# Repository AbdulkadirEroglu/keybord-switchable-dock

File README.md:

# Dual-PC Keyboard Router & Wireless Control Pad

A custom hardware project for sharing one physical USB keyboard between two computers while adding a detachable wireless control pad for call controls, media controls, macros, status feedback, and target selection.

The design prioritizes **reliability, recoverability, wired PC connections, explicit physical control, and independent debug paths**.

## System Overview

The project consists of two custom devices:

1. **Main Dock / Keyboard Router (v2)**
   - Accepts a normal USB keyboard (USB-C).
   - Connects to both Personal and Work PCs over USB and appears as a keyboard to each.
   - Routes keyboard/HID reports to the selected target.
   - Receives the pad's events and selector state over BLE.
   - Powered by its own **USB-C PD charger** (asks for 9 V; a 30 W charger is used). It never draws power from, or back-feeds, the PCs.
   - Chips on the board, built by **JLCPCB** (machine assembly); two through-hole parts are hand-soldered.

2. **Wireless Control Pad** (to be redesigned; current plan below)
   - Detachable and battery powered.
   - 12 mechanical keys.
   - Two rotary encoders with push switches.
   - 36 addressable RGB LEDs.
   - 1.69" colour IPS display (SPI).
   - Physical `PERSONAL | OFF | WORK` metal toggle switch.
   - Li-ion 21700 battery pack, charged while docked.
   - BLE is the normal data link; the pogo UART is reserved for diagnostics/recovery.

## High-Level Architecture

```text
┌──────────── WIRELESS CONTROL PAD ────────────┐
│ Pico 2 WH (RP2350 + CYW43439)   [v1 plan]    │
│ keys, encoders, RGB, display, selector,      │
│ battery + charger                            │
└──────────┬──────────────────────┬────────────┘
           │ BLE                  │ 7-pin magnetic pogo (5 V, DET, UART)
           ▼                      ▼
┌────────────────────── MAIN DOCK (v2) ──────────────────────┐
│ ESP32-C3-MINI-1 (BLE) ── UART ──┐                          │
│                                 ▼                          │
│ keyboard ═ USB-C ═ PIO-USB ═► RP2354A A ═ USB ═► PERSONAL  │
│                                 │ UART, RUN, BOOTSEL, SWD  │
│                                 ▼                          │
│                             RP2354A B ═══ USB ═► WORK      │
│                                                            │
│ USB-C PD charger ─ CH224A (9 V) ─ TPS54331 5 V ─ 3.3 V LDO │
└────────────────────────────────────────────────────────────┘
```

## Main Hardware

### Dock (v2)

| Function | Part |
|---|---|
| Keyboard host + Personal PC endpoint | RP2354A **A** (RP2350 with 2 MB flash, QFN-60): Pico-PIO-USB host + native USB device |
| Work PC endpoint | RP2354A **B** (native USB device) |
| BLE to the pad | ESP32-C3-MINI-1-H4X module (pre-certified, PCB antenna), UART to A |
| Power input | USB-C, CH224A PD sink (9 V, I2C status to A), SMBJ15A TVS |
| 5 V | TPS54331 buck (5.16 V, 3 A), SLO0630H6R8MTT 6.8 µH, SS54 |
| 3.3 V | AMS1117-3.3 |
| Keyboard VBUS | SY6280AAC, 1.0 A, switched on only when a keyboard is detected on CC |
| Pad 5 V (pogo) | SY6280AAC, 1.45 A, switched on in hardware when the pad is docked (DET) |
| ESD | TPD4E1U06 on every USB-C port and the pogo contacts |
| Connectors | 4 × USB-C (TYPE-C-31-M-12); 7-pin JST-XH header to the pogo board in the dock lid (straight 7-pin magnetic pogo contacts) |
| Crystals | ABM8-272-T3 (Raspberry Pi's recommended part) |

Every part, its value and LCSC number: [`hardware/dock-v2/DOCK_CONNECTIONS.md`](hardware/dock-v2/DOCK_CONNECTIONS.md). Why each was chosen: `docs/dock-v2-*.md`.

### Pad (v1 plan, to be redesigned)

| Function | Selected Part / Design |
|---|---|
| Pad MCU / wireless | Raspberry Pi Pico 2 WH, socketed (on-board buck-boost 3.3 V) |
| Pad GPIO expander | TCA9555 |
| Pad charger | TP4056 (switchable ≈ 146 / 510 mA, NTC 0–45 °C, Pico-controlled enable for a 70–80 % docked window) |
| Pad power path | TPS2116 (pogo 5 V priority, battery fallback) |
| Cell protection | DW01A + FS8205A |
| Battery | 2 × Samsung SDI INR21700-50E in parallel (3.6 V, ≈ 9.8 Ah Li-ion), dual 21700 holder |
| RGB 5 V boost | TPS61023 |
| RGB logic buffer | SN74AHCT1G125 |
| RGB LEDs | 36 × SK6812MINI-E (reverse mount) |
| Keys | 12 × Razer Yellow Linear (3-pin MX) in Kailh hot-swap sockets, FR4 plate |
| Encoders | 2 × Bourns PEC11R-4220F-S0024 (24 detents, push switch) |
| Target selector | Metal SPDT ON-OFF-ON toggle |
| Display | 1.69" 240×280 IPS TFT, ST7789, SPI, PWM backlight |

## Target Selection

The physical selector is located on the **control pad**, not the dock.

```text
PERSONAL
   │
  OFF
   │
 WORK
```

The mechanical switch is the source of truth. Its state travels:

```text
Toggle → Pad → BLE → ESP32-C3 → UART → RP2354A A
```

If the pad/BLE connection is lost, the dock must eventually release all active HID states and enter `OFF`.

## Communications

- Keyboard → RP2354A A: USB host (Pico-PIO-USB)
- RP2354A A → Personal PC: USB HID (native USB)
- RP2354A A ↔ RP2354A B: 1 Mbaud+ UART; B → Work PC: USB HID
- Pad ↔ dock: BLE (ESP32-C3 central, pad peripheral), ESP32-C3 ↔ A: UART
- Pogo UART (A's PIO UART): debug/recovery only

The internal UART protocol uses framed binary packets:

```text
SOF | TYPE | SEQ | LEN | PAYLOAD | CRC
```

Normal HID reports may be fire-and-forget. Critical control operations can require acknowledgement.

## Fail-Safe Philosophy

The design should fail toward **released keys and no routing**, not toward a stuck input.

- Target change → release the previous endpoint before changing the route.
- `OFF` → release both endpoints.
- BLE/pad timeout → release all and route OFF.
- A ↔ B link timeout → B sends a released state and idles; A can reset B.
- Keyboard faults → A power-cycles the keyboard's VBUS.
- Every MCU has a physical recovery path, and A can reflash B (SWD) and the ESP32-C3 (UART) from the Personal PC.

## Mechanical Baseline

- **Dock:** PCB 100 × 100 mm, 2 layers. PC cables leave at the back, the keyboard at the left, the charger at the right. **The pad sits on top of the dock:** the pogo contacts are on a small board in the dock lid, cabled to the dock board.
- **Pad (v1 plan):** wedge enclosure ≈ 160 × 110–120 mm, front ≈ 25 mm, back ≈ 44 mm, battery at the back under the display/encoder row.

Docking contacts (dock side), magnets on both sides:

```text
GND | +5V | DET | RX | TX | +5V | GND
```

## Repository Layout

```text
dock-pad/
├── hardware/
│   ├── dock-v2/        v2 dock: KiCad project, DOCK_CONNECTIONS.md, PCB_PLACEMENT.md
│   ├── dock/           v1 dock (Pico modules), reference
│   ├── pad/            pad (v1 plan)
│   ├── pogo/           pad pogo board
│   ├── libraries/      shared symbols/footprints/3D models (THIRD_PARTY.md)
│   ├── reference/      Raspberry Pi RP2350A Minimal design (MIT)
│   └── tools/          RPi core-layout copy script, dock v2 connection model and wiring checker
├── mechanical/
├── firmware/
├── datasheets/
├── docs/               dock v2 design decisions (dock-v2-*.md), pad drawings
├── README.md
└── DESIGN.md
```

## Current Project State

- **Dock v2 (branch `dock-v2`):** every part decided and placed on the six schematic sheets (154 parts, values, footprints, LCSC numbers). Next: wiring the schematic by hand from [DOCK_WIRING.md](hardware/dock-v2/DOCK_WIRING.md) (component by component; the circuit is explained in DOCK_CONNECTIONS.md) (checked with `hardware/tools/dock_v2_connections/check_wiring.py`), then placement and routing on a 4-layer board. The order cost will be calculated when the PCB is ready.
- **Pad:** being redesigned. Decided so far: **ESP32-S3-MINI-1-N8** (MCU + BLE, JLC assembly), the pad **sits on top of the dock** with its pogo board in the floor, **1 × 21700-50E** with an **ETA6003** switching charger (power path), charged only on the dock, TLV75733P 3.3 V LDO, direct-GPIO keys/encoders, SK6812MINI-E + XL-2020 LEDs on a TPS61023 5 V boost, Meon 1.69" ST7789 module. Decisions: `docs/pad-v2-*.md`. The rest of `hardware/pad/` is still the v1 plan.
- **v1 dock:** complete (routed, DRC clean) on `master`; superseded by v2.

See [DESIGN.md](DESIGN.md) for the engineering baseline.

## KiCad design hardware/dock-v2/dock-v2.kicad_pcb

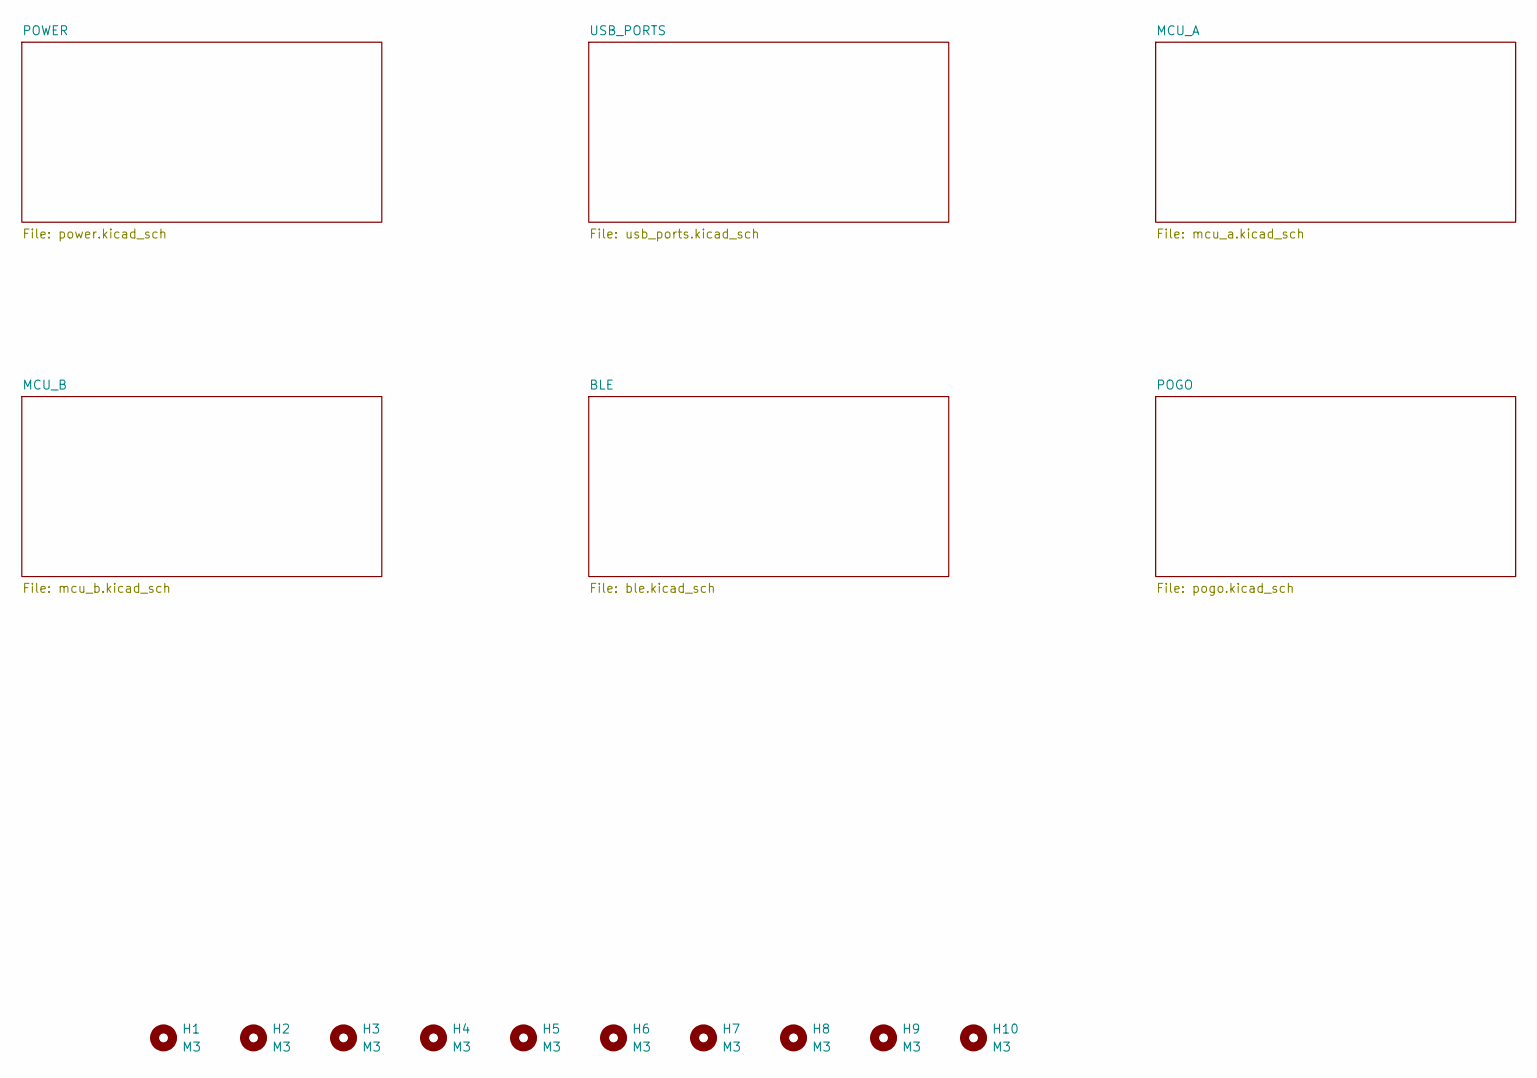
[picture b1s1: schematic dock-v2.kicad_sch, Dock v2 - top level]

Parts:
H1, H2, H3, H4, H5, H6, H7, H8, H9, H10: M3; MountingHole_3.2mm_M3

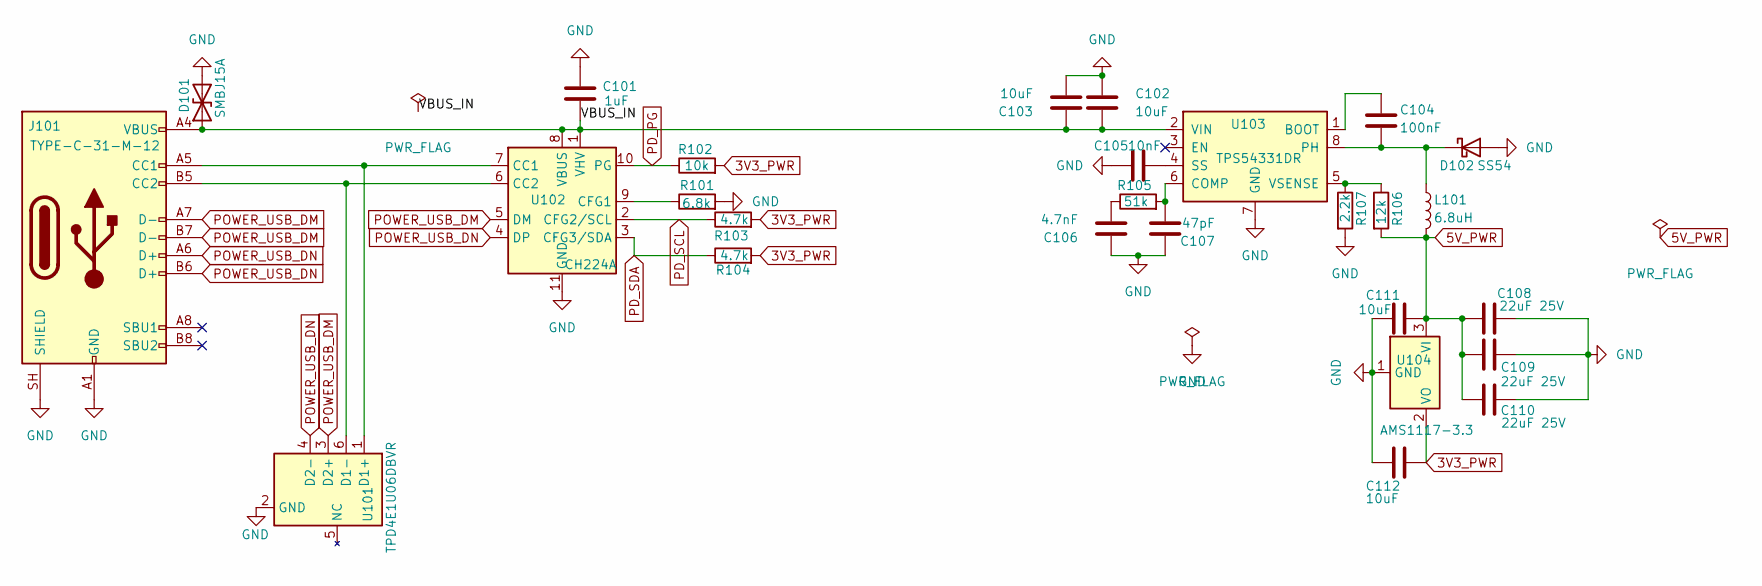
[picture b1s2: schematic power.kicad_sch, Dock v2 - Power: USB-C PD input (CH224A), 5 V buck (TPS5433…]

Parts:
C101: 1uF; C_0603_1608Metric; LCSC C15849
C102, C103, C111, C112: 10uF; C_0805_2012Metric; LCSC C15850
C104: 100nF; C_0402_1005Metric; LCSC C1525
C105: 10nF; C_0402_1005Metric; LCSC C15195
C106: 4.7nF; C_0402_1005Metric; LCSC C1538
C107: 47pF; C_0402_1005Metric; LCSC C1567
C108, C109, C110: 22uF 25V; C_1206_3216Metric; LCSC C12891
D101: SMBJ15A; D_SMB; LCSC C113988
D102: SS54; D_SMC; LCSC C22452
J101: TYPE-C-31-M-12; USB_C_Receptacle_HRO_TYPE-C-31-M-12; LCSC C165948
L101: 6.8uH; L_TechFuse_SL0630; LCSC C207841
R101: 6.8k; R_0402_1005Metric; LCSC C25917
R102: 10k; R_0402_1005Metric; LCSC C25744
R103, R104: 4.7k; R_0402_1005Metric; LCSC C25900
R105: 51k; R_0402_1005Metric; LCSC C25794
R106: 12k; R_0402_1005Metric; LCSC C25752
R107: 2.2k; R_0402_1005Metric; LCSC C25879
U101: TPD4E1U06DBVR; SOT-23-6; LCSC C124691
U102: CH224A; SSOP-10-1EP_3.9x4.9mm_P1mm_EP2.1x3.3mm; LCSC C42459160
U103: TPS54331DR; SOIC-8_3.9x4.9mm_P1.27mm; LCSC C9865
U104: AMS1117-3.3; SOT-223-3_TabPin2; LCSC C6186

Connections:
3V3_PWR: C112.1, R102.2, R103.2, R104.2, U104.2 (VO); also elsewhere on the board
5V_PWR: C108.1, C109.2, C110.1, C111.1, L101.2, R106.2, U104.3 (VI); also elsewhere on the board
/POWER/VBUS_IN: C101.2, C102.2, C103.1, D101.1 (A1), J101.A4 (VBUS), J101.A9 (VBUS), J101.B4 (VBUS), J101.B9 (VBUS), U102.1 (VHV), U102.8 (VBUS), U103.2 (VIN)
GND: C101.1, C102.1, C103.2, C105.1, C106.1, C107.1, C108.2, C109.1, C110.2, C111.2, C112.2, D101.2 (A2), D102.2 (A), J101.A1 (GND), J101.A12 (GND), J101.B1 (GND), J101.B12 (GND), J101.SH (SHIELD), R101.2, R107.2, U101.2 (GND), U102.11 (GND), U103.7 (GND), U104.1 (GND); also elsewhere on the board
unnamed: C106.2, R105.1
unnamed: C104.2, D102.1 (K), L101.1, U103.8 (PH)
unnamed: J101.A5 (CC1), U101.1 (D1+), U102.7 (CC1)
unnamed: J101.B5 (CC2), U101.6 (D1-), U102.6 (CC2)
unnamed: R101.1, U102.9 (CFG1)
unnamed: C104.1, U103.1 (BOOT)
unnamed: C107.2, R105.2, U103.6 (COMP)
unnamed: C105.2, U103.4 (SS)
unnamed: R106.1, R107.1, U103.5 (VSENSE)
PD_PG: R102.1, U102.10 (PG); also elsewhere on the board
PD_SCL: R103.1, U102.2 (CFG2/SCL); also elsewhere on the board
PD_SDA: R104.1, U102.3 (CFG3/SDA); also elsewhere on the board
POWER_USB_DM: J101.A7 (D-), J101.B7 (D-), U101.3 (D2+), U102.5 (DM)
POWER_USB_DN: J101.A6 (D+), J101.B6 (D+), U101.4 (D2-), U102.4 (DP)

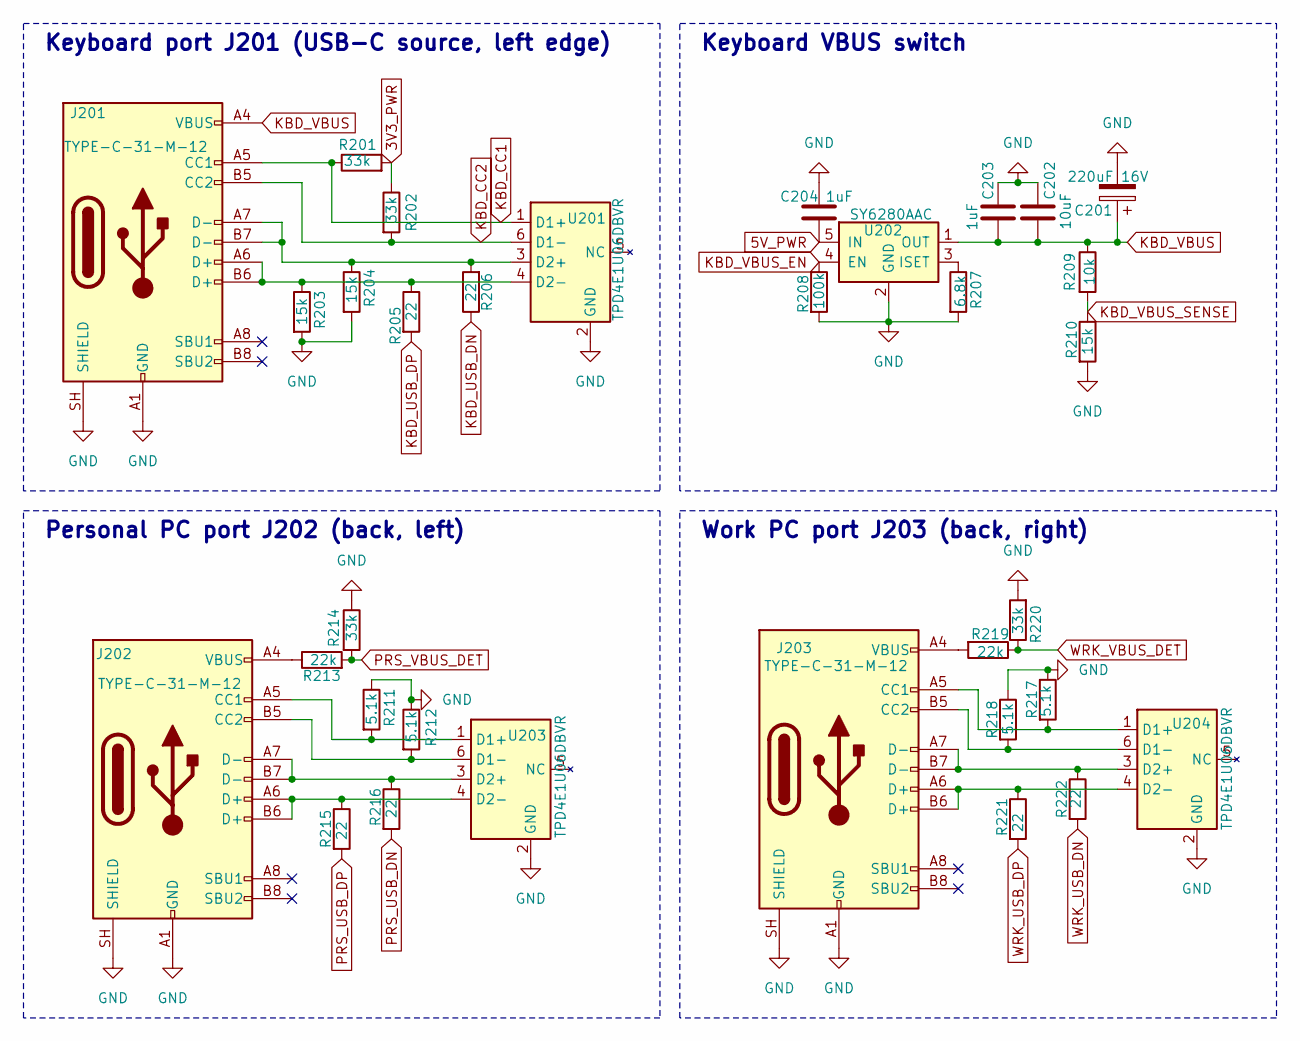
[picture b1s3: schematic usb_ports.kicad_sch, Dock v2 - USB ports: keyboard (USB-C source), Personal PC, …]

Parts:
C201: 220uF 16V; CP_Radial_D6.3mm_P5.00mm
C202: 10uF; C_0805_2012Metric; LCSC C15850
C203, C204: 1uF; C_0402_1005Metric; LCSC C52923
J201, J202, J203: TYPE-C-31-M-12; USB_C_Receptacle_HRO_TYPE-C-31-M-12; LCSC C165948
R201, R202, R214, R220: 33k; R_0402_1005Metric; LCSC C25779
R203, R204, R210: 15k; R_0402_1005Metric; LCSC C25756
R205, R206, R215, R216, R221, R222: 22; R_0402_1005Metric; LCSC C25092
R207: 6.8k; R_0402_1005Metric; LCSC C25917
R208: 100k; R_0402_1005Metric; LCSC C25741
R209: 10k; R_0402_1005Metric; LCSC C25744
R211, R212, R217, R218: 5.1k; R_0402_1005Metric; LCSC C25905
R213, R219: 22k; R_0402_1005Metric; LCSC C25768
U201, U203, U204: TPD4E1U06DBVR; SOT-23-6; LCSC C124691
U202: SY6280AAC; SOT-23-5; LCSC C55136

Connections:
3V3_PWR: R201.2, R202.1; also elsewhere on the board
5V_PWR: C204.2, U202.5 (IN); also elsewhere on the board
GND: C201.2, C202.1, C203.2, C204.1, J201.A1 (GND), J201.A12 (GND), J201.B1 (GND), J201.B12 (GND), J201.SH (SHIELD), J202.A1 (GND), J202.A12 (GND), J202.B1 (GND), J202.B12 (GND), J202.SH (SHIELD), J203.A1 (GND), J203.A12 (GND), J203.B1 (GND), J203.B12 (GND), J203.SH (SHIELD), R203.2, R204.2, R207.2, R208.2, R210.2, R211.1, R212.1, R214.1, R217.1, R218.1, R220.2, U201.2 (GND), U202.2 (GND), U203.2 (GND), U204.2 (GND); also elsewhere on the board
KBD_CC1: J201.A5 (CC1), R201.1, U201.1 (D1+); also elsewhere on the board
KBD_CC2: J201.B5 (CC2), R202.2, U201.6 (D1-); also elsewhere on the board
KBD_USB_DN: R206.1; also elsewhere on the board
KBD_USB_DP: R205.2; also elsewhere on the board
KBD_VBUS: C201.1, C202.2, C203.1, J201.A4 (VBUS), J201.A9 (VBUS), J201.B4 (VBUS), J201.B9 (VBUS), R209.1, U202.1 (OUT)
KBD_VBUS_EN: R208.1, U202.4 (EN); also elsewhere on the board
KBD_VBUS_SENSE: R209.2, R210.1; also elsewhere on the board
unnamed: J202.A5 (CC1), R211.2, U203.1 (D1+)
unnamed: J202.B5 (CC2), R212.2, U203.6 (D1-)
unnamed: J202.A4 (VBUS), J202.A9 (VBUS), J202.B4 (VBUS), J202.B9 (VBUS), R213.1
unnamed: J203.A5 (CC1), R217.2, U204.1 (D1+)
unnamed: J203.B5 (CC2), R218.2, U204.6 (D1-)
unnamed: J203.A4 (VBUS), J203.A9 (VBUS), J203.B4 (VBUS), J203.B9 (VBUS), R219.2
unnamed: J201.A7 (D-), J201.B7 (D-), R204.1, R206.2, U201.3 (D2+)
unnamed: J201.A6 (D+), J201.B6 (D+), R203.1, R205.1, U201.4 (D2-)
unnamed: R207.1, U202.3 (ISET)
unnamed: J202.A7 (D-), J202.B7 (D-), R216.1, U203.3 (D2+)
unnamed: J202.A6 (D+), J202.B6 (D+), R215.1, U203.4 (D2-)
unnamed: J203.A7 (D-), J203.B7 (D-), R222.1, U204.3 (D2+)
unnamed: J203.A6 (D+), J203.B6 (D+), R221.1, U204.4 (D2-)
PRS_USB_DN: R216.2; also elsewhere on the board
PRS_USB_DP: R215.2; also elsewhere on the board
PRS_VBUS_DET: R213.2, R214.2; also elsewhere on the board
WRK_USB_DN: R222.2; also elsewhere on the board
WRK_USB_DP: R221.2; also elsewhere on the board
WRK_VBUS_DET: R219.1, R220.1; also elsewhere on the board

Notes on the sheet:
Keyboard VBUS switch
Keyboard port J201 (USB-C source, left edge)
Personal PC port J202 (back, left)
Work PC port J203 (back, right)

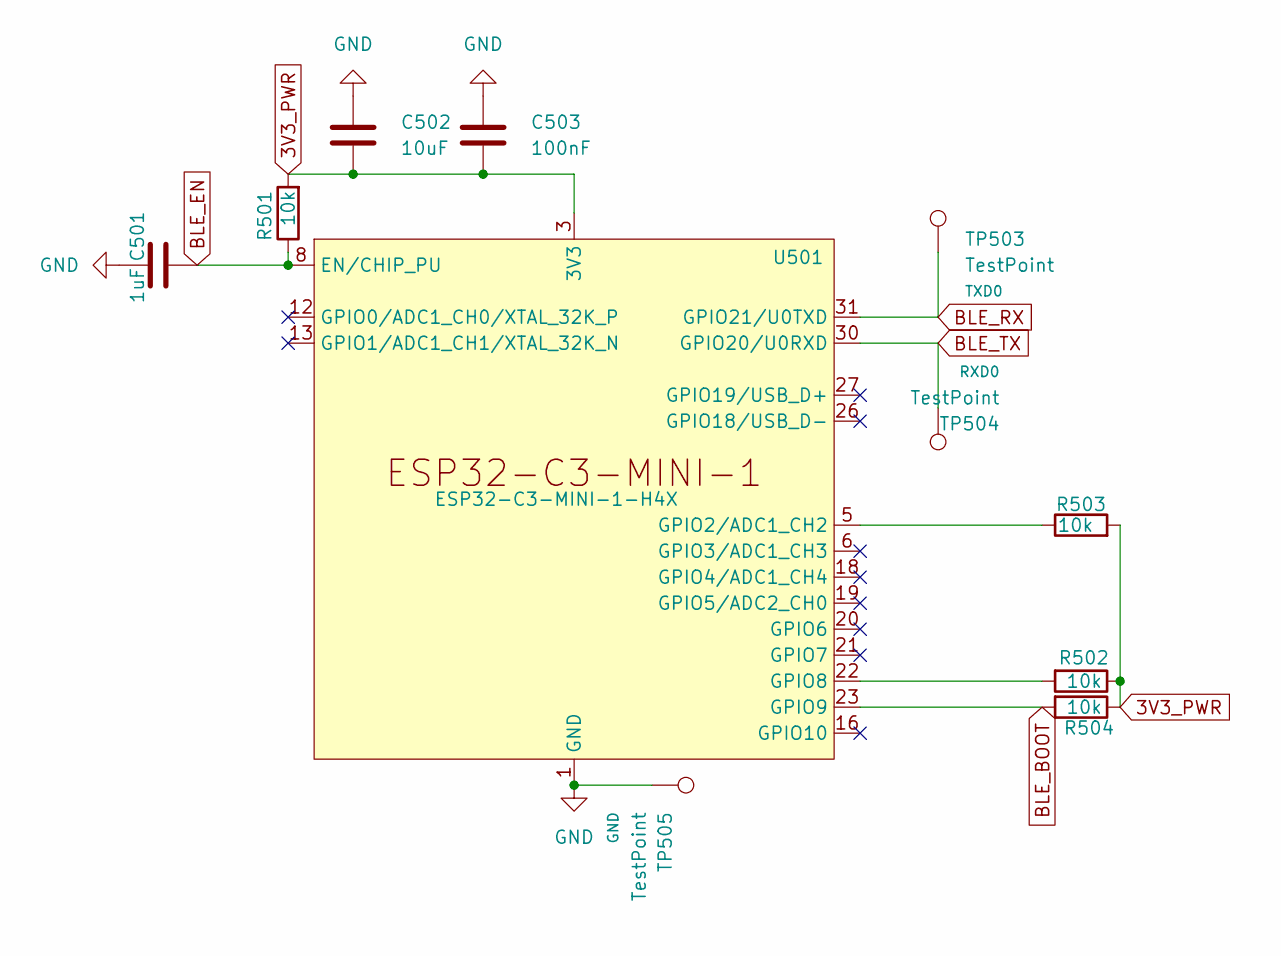
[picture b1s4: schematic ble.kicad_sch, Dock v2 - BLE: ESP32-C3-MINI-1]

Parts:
C501: 1uF; C_0402_1005Metric; LCSC C52923
C502: 10uF; C_0805_2012Metric; LCSC C15850
C503: 100nF; C_0402_1005Metric; LCSC C1525
R501, R502, R503, R504: 10k; R_0402_1005Metric; LCSC C25744
TP503, TP504, TP505: TestPoint; TestPoint_Pad_D1.0mm
U501: ESP32-C3-MINI-1-H4X; ESP32-C3-MINI-1; LCSC C41349510

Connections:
3V3_PWR: C502.2, C503.2, R501.2, R502.1, R503.2, R504.1, U501.3 (3V3); also elsewhere on the board
BLE_BOOT: R504.2, U501.23 (GPIO9); also elsewhere on the board
BLE_EN: C501.2, R501.1, U501.8 (EN/CHIP_PU); also elsewhere on the board
BLE_RX: TP503.1 (1_1), U501.31 (GPIO21/U0TXD); also elsewhere on the board
BLE_TX: TP504.1 (1_1), U501.30 (GPIO20/U0RXD); also elsewhere on the board
GND: C501.1, C502.1, C503.1, TP505.1 (1_1), U501.1 (GND), U501.2 (GND), U501.11 (GND), U501.14 (GND), U501.36 (GND), U501.37 (GND), U501.38 (GND), U501.39 (GND), U501.40 (GND), U501.41 (GND), U501.42 (GND), U501.43 (GND), U501.44 (GND), U501.45 (GND), U501.46 (GND), U501.47 (GND), U501.48 (GND), U501.49 (GND), U501.50 (GND), U501.51 (GND), U501.52 (GND), U501.53 (GND); also elsewhere on the board
unnamed: R503.1, U501.5 (GPIO2/ADC1_CH2)
unnamed: R502.2, U501.22 (GPIO8)

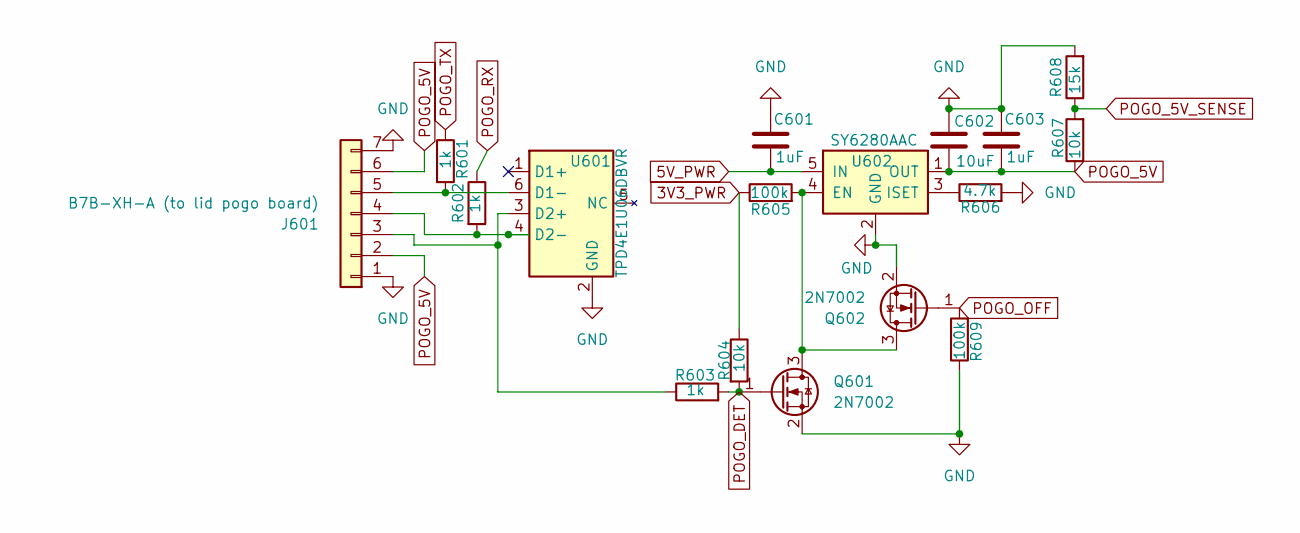
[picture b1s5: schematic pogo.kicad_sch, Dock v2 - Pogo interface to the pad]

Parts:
C601, C603: 1uF; C_0402_1005Metric; LCSC C52923
C602: 10uF; C_0805_2012Metric; LCSC C15850
J601: B7B-XH-A (to lid pogo board); JST_XH_B7B-XH-A_1x07_P2.50mm_Vertical_EdgeTrim; LCSC C144398
Q601, Q602: 2N7002; SOT-23; LCSC C8545
R601, R602, R603: 1k; R_0402_1005Metric; LCSC C11702
R604, R607: 10k; R_0402_1005Metric; LCSC C25744
R605, R609: 100k; R_0402_1005Metric; LCSC C25741
R606: 4.7k; R_0402_1005Metric; LCSC C25900
R608: 15k; R_0402_1005Metric; LCSC C25756
U601: TPD4E1U06DBVR; SOT-23-6; LCSC C124691
U602: SY6280AAC; SOT-23-5; LCSC C55136

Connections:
3V3_PWR: R604.1, R605.1; also elsewhere on the board
5V_PWR: C601.2, U602.5 (IN); also elsewhere on the board
GND: C601.1, C602.1, C603.1, J601.1, J601.7, Q601.2 (S), Q602.2 (S), R606.2, R608.2, R609.1, U601.2 (GND), U602.2 (GND); also elsewhere on the board
unnamed: J601.3, R603.1, U601.3 (D2+)
unnamed: J601.4, R602.2, U601.4 (D2-)
unnamed: J601.5, R601.2, U601.6 (D1-)
unnamed: Q601.3 (D), Q602.3 (D), R605.2, U602.4 (EN)
unnamed: R606.1, U602.3 (ISET)
POGO_5V: C602.2, C603.2, J601.2, J601.6, R607.1, U602.1 (OUT)
POGO_5V_SENSE: R607.2, R608.1; also elsewhere on the board
POGO_DET: Q601.1 (G), R603.2, R604.2; also elsewhere on the board
POGO_OFF: Q602.1 (G), R609.2; also elsewhere on the board
POGO_RX: R602.1; also elsewhere on the board
POGO_TX: R601.1; also elsewhere on the board

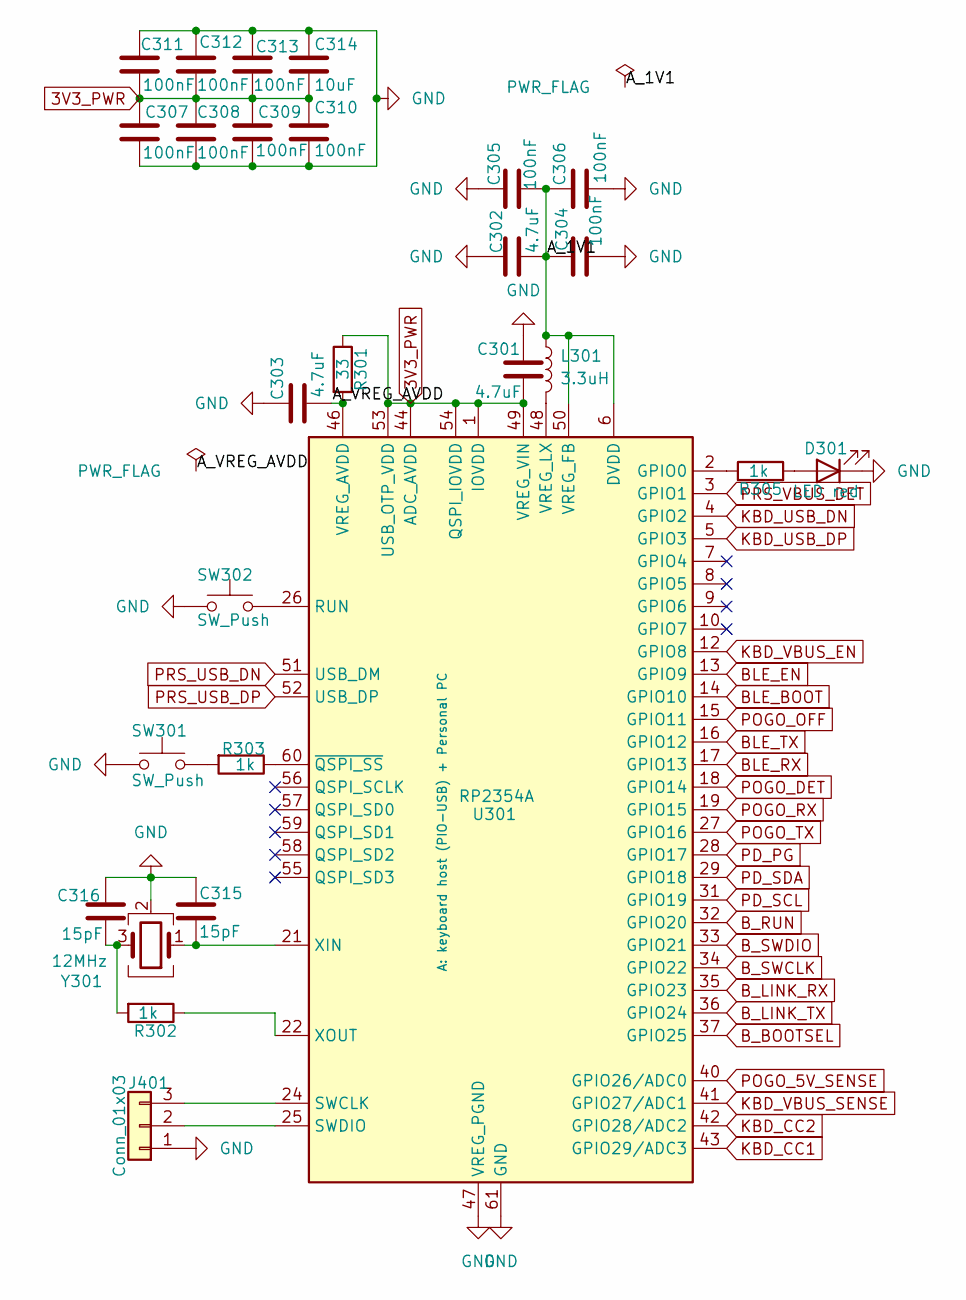
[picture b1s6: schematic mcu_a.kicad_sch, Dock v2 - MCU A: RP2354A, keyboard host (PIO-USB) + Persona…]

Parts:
C301, C302: 4.7uF; C_0402_RPi_Wide; LCSC C23733
C303: 4.7uF; C_0402_1005Metric; LCSC C23733
C304, C305, C306, C307, C308, C309, C310, C311, C312, C313: 100nF; C_0402_1005Metric; LCSC C1525
C314: 10uF; C_0805_2012Metric; LCSC C15850
C315, C316: 15pF; C_0402_1005Metric; LCSC C1548
D301: LED red; LED_0603_1608Metric; LCSC C2286
J401: Conn_01x03; PinHeader_1x03_P2.54mm_Vertical
L301: 3.3uH; L_Abracon_AOTA-B201610S3R3_0806; LCSC C42411119
R301: 33; R_0402_1005Metric; LCSC C25105
R302, R303, R305: 1k; R_0402_1005Metric; LCSC C11702
SW301, SW302: SW_Push; SW_Push_1P1T_XKB_TS-1187A; LCSC C318884
U301: RP2354A; RP2350A_QFN-60_RPi_Vias; LCSC C41378174
Y301: 12MHz; Crystal_SMD_3225-4Pin_3.2x2.5mm; LCSC C20625731

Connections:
3V3_PWR: C301.2, C307.1, C308.1, C309.1, C310.1, C311.2, C312.2, C313.2, C314.2, R301.1, U301.1 (IOVDD), U301.11 (IOVDD), U301.20 (IOVDD), U301.30 (IOVDD), U301.38 (IOVDD), U301.44 (ADC_AVDD), U301.45 (IOVDD), U301.49 (VREG_VIN), U301.53 (USB_OTP_VDD), U301.54 (QSPI_IOVDD); also elsewhere on the board
/MCU_A/A_1V1: C302.2, C304.1, C305.2, C306.1, L301.1, U301.6 (DVDD), U301.23 (DVDD), U301.39 (DVDD), U301.50 (VREG_FB)
/MCU_A/A_VREG_AVDD: C303.2, R301.2, U301.46 (VREG_AVDD)
BLE_BOOT: U301.14 (GPIO10); also elsewhere on the board
BLE_EN: U301.13 (GPIO9); also elsewhere on the board
BLE_RX: U301.17 (GPIO13); also elsewhere on the board
BLE_TX: U301.16 (GPIO12); also elsewhere on the board
B_BOOTSEL: U301.37 (GPIO25); also elsewhere on the board
B_LINK_RX: U301.35 (GPIO23); also elsewhere on the board
B_LINK_TX: U301.36 (GPIO24); also elsewhere on the board
B_RUN: U301.32 (GPIO20); also elsewhere on the board
B_SWCLK: U301.34 (GPIO22); also elsewhere on the board
B_SWDIO: U301.33 (GPIO21); also elsewhere on the board
GND: C301.1, C302.1, C303.1, C304.2, C305.1, C306.2, C307.2, C308.2, C309.2, C310.2, C311.1, C312.1, C313.1, C314.1, C315.1, C316.1, D301.1 (K), J401.1, SW301.1, SW302.1, U301.47 (VREG_PGND), U301.61 (GND), Y301.2 (G), Y301.4 (G); also elsewhere on the board
KBD_CC1: U301.43 (GPIO29/ADC3); also elsewhere on the board
KBD_CC2: U301.42 (GPIO28/ADC2); also elsewhere on the board
KBD_USB_DN: U301.4 (GPIO2); also elsewhere on the board
KBD_USB_DP: U301.5 (GPIO3); also elsewhere on the board
KBD_VBUS_EN: U301.12 (GPIO8); also elsewhere on the board
KBD_VBUS_SENSE: U301.41 (GPIO27/ADC1); also elsewhere on the board
unnamed: C316.2, R302.2, Y301.3
unnamed: D301.2 (A), R305.2
unnamed: J401.2, U301.25 (SWDIO)
unnamed: J401.3, U301.24 (SWCLK)
unnamed: R303.2, SW301.2
unnamed: R305.1, U301.2 (GPIO0)
unnamed: SW302.2, U301.26 (RUN)
unnamed: L301.2, U301.48 (VREG_LX)
unnamed: C315.2, U301.21 (XIN), Y301.1
unnamed: R302.1, U301.22 (XOUT)
unnamed: R303.1, U301.60 (~QSPI_SS)
PD_PG: U301.28 (GPIO17); also elsewhere on the board
PD_SCL: U301.31 (GPIO19); also elsewhere on the board
PD_SDA: U301.29 (GPIO18); also elsewhere on the board
POGO_5V_SENSE: U301.40 (GPIO26/ADC0); also elsewhere on the board
POGO_DET: U301.18 (GPIO14); also elsewhere on the board
POGO_OFF: U301.15 (GPIO11); also elsewhere on the board
POGO_RX: U301.19 (GPIO15); also elsewhere on the board
POGO_TX: U301.27 (GPIO16); also elsewhere on the board
PRS_USB_DN: U301.51 (USB_DM); also elsewhere on the board
PRS_USB_DP: U301.52 (USB_DP); also elsewhere on the board
PRS_VBUS_DET: U301.3 (GPIO1); also elsewhere on the board

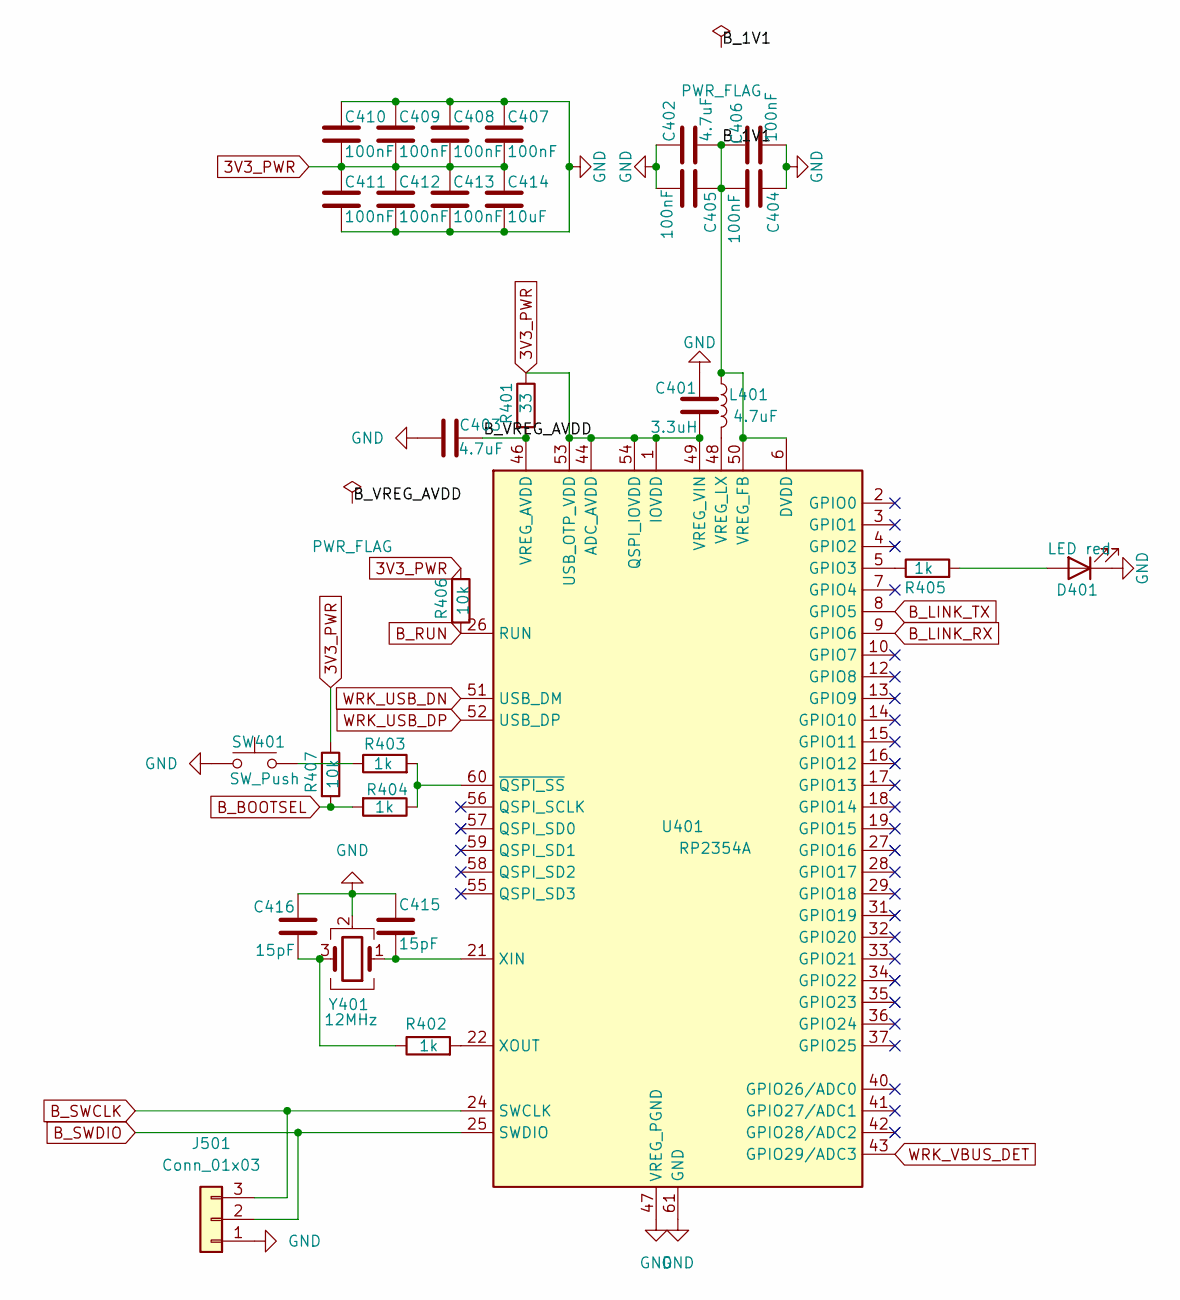
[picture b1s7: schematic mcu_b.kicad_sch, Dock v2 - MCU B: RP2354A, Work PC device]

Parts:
C401, C402: 4.7uF; C_0402_RPi_Wide; LCSC C23733
C403: 4.7uF; C_0402_1005Metric; LCSC C23733
C404, C405, C406, C407, C408, C409, C410, C411, C412, C413: 100nF; C_0402_1005Metric; LCSC C1525
C414: 10uF; C_0805_2012Metric; LCSC C15850
C415, C416: 15pF; C_0402_1005Metric; LCSC C1548
D401: LED red; LED_0603_1608Metric; LCSC C2286
J501: Conn_01x03; PinHeader_1x03_P2.54mm_Vertical
L401: 3.3uH; L_Abracon_AOTA-B201610S3R3_0806; LCSC C42411119
R401: 33; R_0402_1005Metric; LCSC C25105
R402, R403, R404, R405: 1k; R_0402_1005Metric; LCSC C11702
R406, R407: 10k; R_0402_1005Metric; LCSC C25744
SW401: SW_Push; SW_Push_1P1T_XKB_TS-1187A; LCSC C318884
U401: RP2354A; RP2350A_QFN-60_RPi_Vias; LCSC C41378174
Y401: 12MHz; Crystal_SMD_3225-4Pin_3.2x2.5mm; LCSC C20625731

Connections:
3V3_PWR: C401.2, C407.2, C408.2, C409.2, C410.2, C411.1, C412.1, C413.1, C414.1, R401.1, R406.1, R407.1, U401.1 (IOVDD), U401.11 (IOVDD), U401.20 (IOVDD), U401.30 (IOVDD), U401.38 (IOVDD), U401.44 (ADC_AVDD), U401.45 (IOVDD), U401.49 (VREG_VIN), U401.53 (USB_OTP_VDD), U401.54 (QSPI_IOVDD); also elsewhere on the board
/MCU_B/B_1V1: C402.2, C404.2, C405.1, C406.1, L401.1, U401.6 (DVDD), U401.23 (DVDD), U401.39 (DVDD), U401.50 (VREG_FB)
/MCU_B/B_VREG_AVDD: C403.2, R401.2, U401.46 (VREG_AVDD)
B_BOOTSEL: R404.2, R407.2; also elsewhere on the board
B_LINK_RX: U401.9 (GPIO6); also elsewhere on the board
B_LINK_TX: U401.8 (GPIO5); also elsewhere on the board
B_RUN: R406.2, U401.26 (RUN); also elsewhere on the board
B_SWCLK: J501.3, U401.24 (SWCLK); also elsewhere on the board
B_SWDIO: J501.2, U401.25 (SWDIO); also elsewhere on the board
GND: C401.1, C402.1, C403.1, C404.1, C405.2, C406.2, C407.1, C408.1, C409.1, C410.1, C411.2, C412.2, C413.2, C414.2, C415.1, C416.2, D401.1 (K), J501.1, SW401.1, U401.47 (VREG_PGND), U401.61 (GND), Y401.2 (G), Y401.4 (G); also elsewhere on the board
unnamed: C416.1, R402.1, Y401.3
unnamed: D401.2 (A), R405.2
unnamed: R403.1, SW401.2
unnamed: R405.1, U401.5 (GPIO3)
unnamed: L401.2, U401.48 (VREG_LX)
unnamed: C415.2, U401.21 (XIN), Y401.1
unnamed: R402.2, U401.22 (XOUT)
unnamed: R403.2, R404.1, U401.60 (~QSPI_SS)
WRK_USB_DN: U401.51 (USB_DM); also elsewhere on the board
WRK_USB_DP: U401.52 (USB_DP); also elsewhere on the board
WRK_VBUS_DET: U401.43 (GPIO29/ADC3); also elsewhere on the board

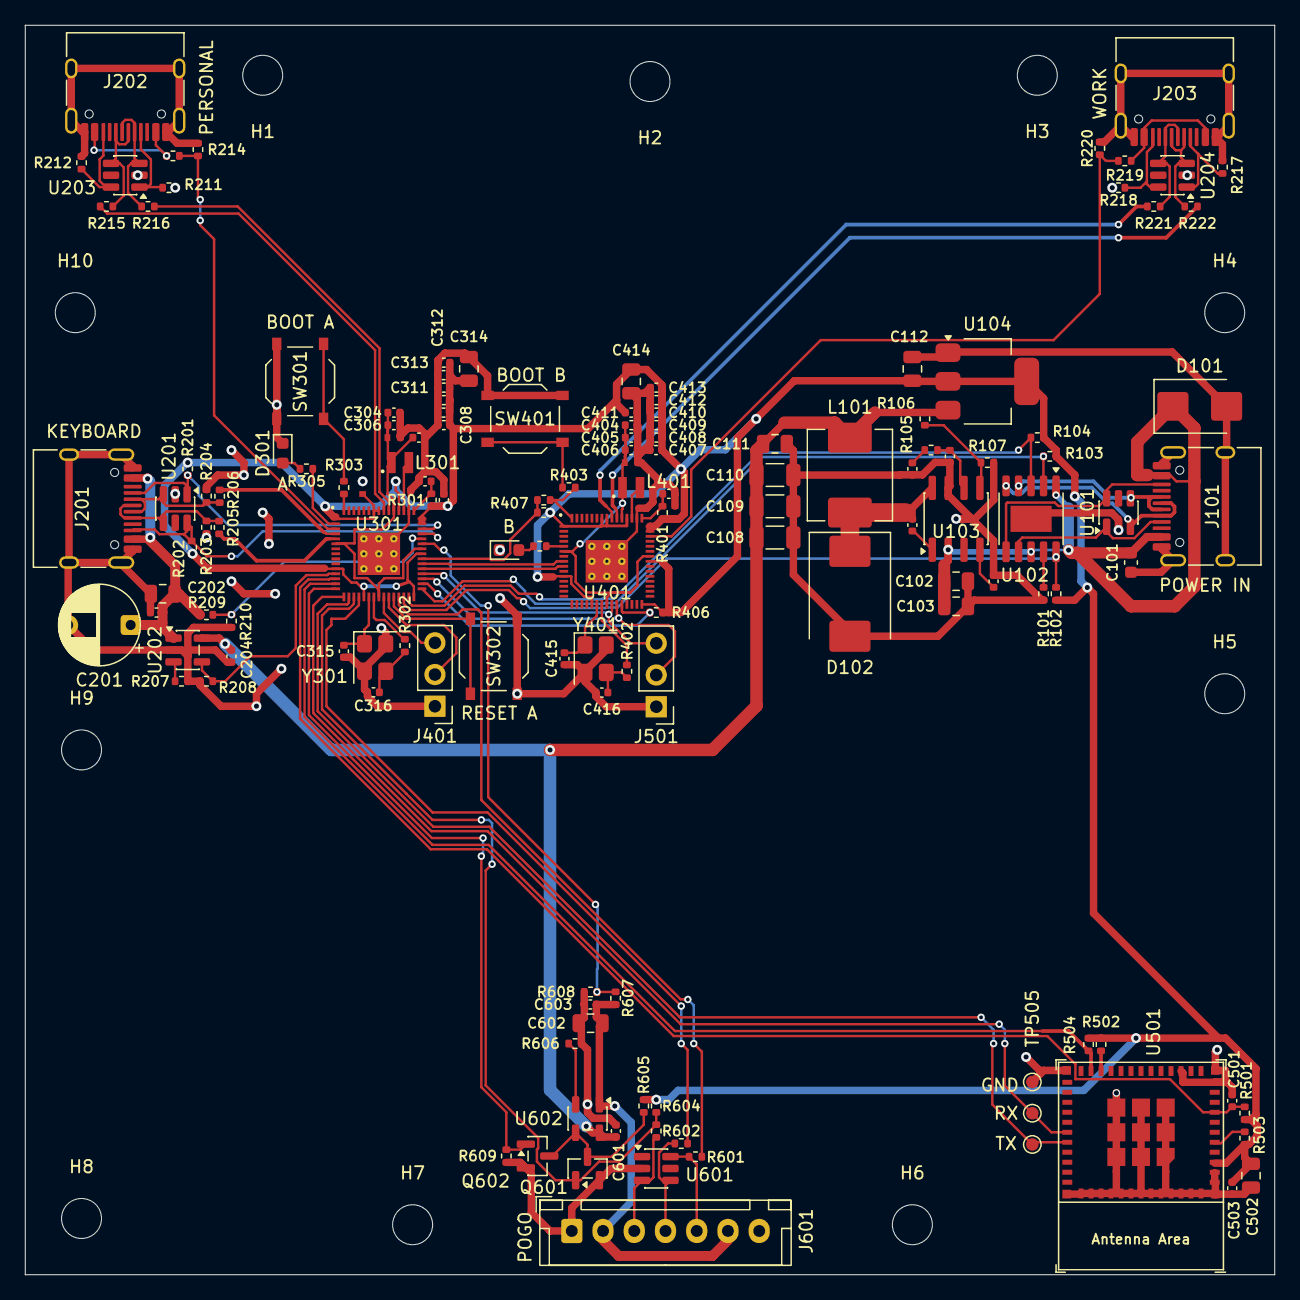
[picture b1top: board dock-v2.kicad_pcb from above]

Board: 2 copper layers, 100.0 x 100.0 mm, 154 parts (0 on the bottom side), 90 nets.
